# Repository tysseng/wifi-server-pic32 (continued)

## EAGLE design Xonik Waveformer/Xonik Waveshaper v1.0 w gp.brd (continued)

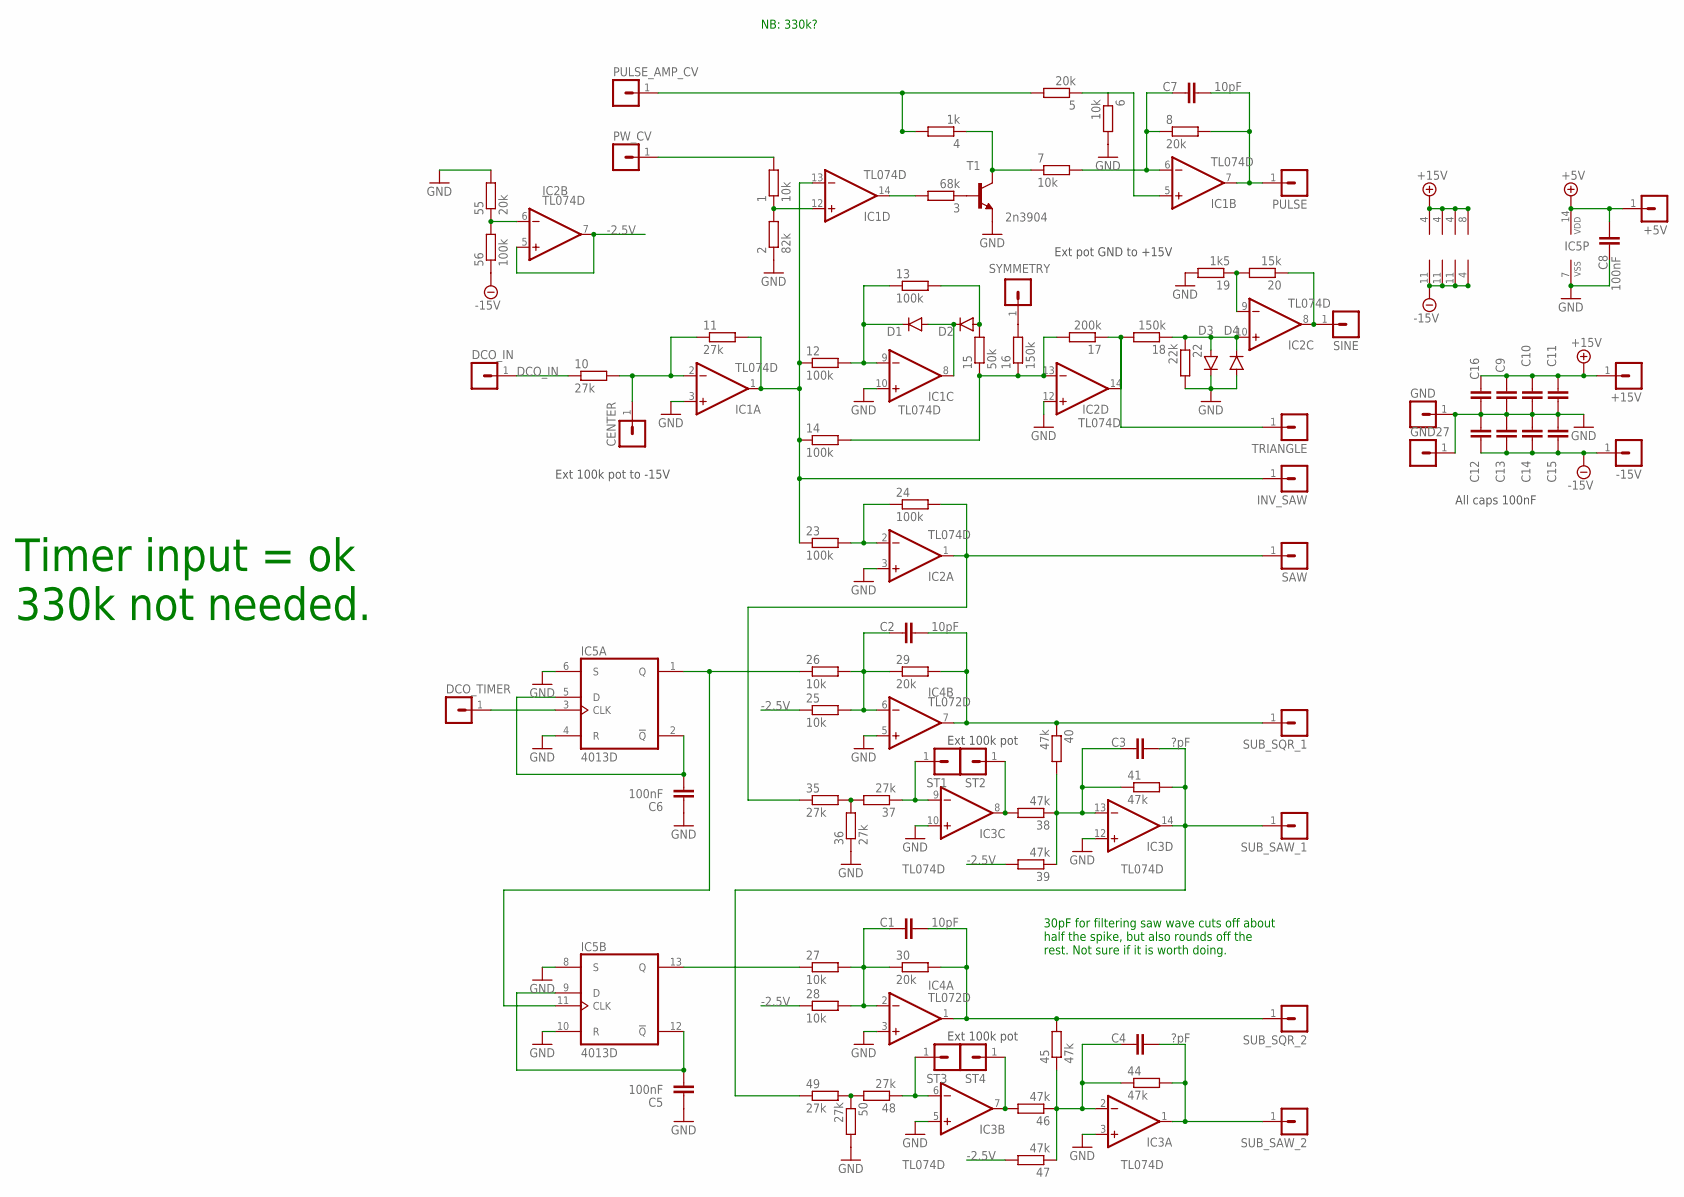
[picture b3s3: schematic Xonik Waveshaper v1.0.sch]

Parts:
1, 6, 7, 25, 26, 27, 28: 10k; R0805
2: 82k; R0805
3: 68k; R0805
4: 1k; R0805
5, 8, 29, 30, 55: 20k; R0805
10, 11, 35, 36, 37, 48, 49, 50: 27k; R0805
12, 13, 14, 23, 24, 56: 100k; R0805
15: 50k; R0805
16, 18: 150k; R0805
17: 200k; R0805
19: 1k5; R0805
20: 15k; R0805
22: 22k; R0805
38, 39, 40, 41, 44, 45, 46, 47: 47k; R0805
+5V, +15V: MA01-1JP; SIP-PIN01-1J
-15V: MA01-1JP; SIP-PIN01-1J
C1, C2, C7: 10pF; C0805
C3, C4: ?pF; C0805
C5, C6, C8: 100nF; C0805
C9, C10, C11, C12, C13, C14, C15, C16: 100nF; C0603K
CENTER: MA01-1JP; SIP-PIN01-1J
D1, D2, D3, D4: 1N41480805; D0805-J
DCO_IN: MA01-1JP; SIP-PIN01-1J
DCO_TIMER: MA01-1JP; SIP-PIN01-1J
GND, GND27: MA01-1JP; SIP-PIN01-1J
IC1, IC2, IC3: TL074D; SO14
IC4: TL072D; SO08J
IC5: 4013D; SO14J
INV_SAW: MA01-1JP; SIP-PIN01-1J
PULSE: MA01-1JP; SIP-PIN01-1J
PULSE_AMP_CV: MA01-1JP; SIP-PIN01-1J
PW_CV: MA01-1JP; SIP-PIN01-1J
SAW: MA01-1JP; SIP-PIN01-1J
SINE: MA01-1JP; SIP-PIN01-1J
ST1, ST2, ST3, ST4: MA01-1JP; SIP-PIN01-1J
SUB_SAW_1, SUB_SAW_2: MA01-1JP; SIP-PIN01-1J
SUB_SQR_1, SUB_SQR_2: MA01-1JP; SIP-PIN01-1J
SYMMETRY: MA01-1JP; SIP-PIN01-1J
T1: 2n3904; SOT23-BEC
TRIANGLE: MA01-1JP; SIP-PIN01-1J

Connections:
+5V: +5V.1, C8.2, IC5.14 (VDD)
+15V: +15V.1, C9.2, C10.2, C11.2, C16.2, IC1.4 (V+), IC2.4 (V+), IC3.4 (V+), IC4.8 (V+)
-2.5V: 25.1, 28.1, 39.2, 47.2, IC2.5 (+IN), IC2.7 (OUT)
-15V: 56.1, -15V.1, C12.1, C13.1, C14.1, C15.1, IC1.11 (V-), IC2.11 (V-), IC3.11 (V-), IC4.4 (V-)
AMP_CV: 4.2, 5.2, PULSE_AMP_CV.1
DCO_IN: 10.1, DCO_IN.1
GND: 2.1, 6.2, 19.2, 22.2, 36.1, 50.2, 55.2, C5.1, C6.1, C8.1, C9.1, C10.1, C11.1, C12.2, C13.2, C14.2, C15.2, C16.1, D3.C, D4.A, GND.1, GND27.1, IC1.3 (+IN), IC1.10 (+IN), IC2.3 (+IN), IC2.12 (+IN), IC3.3 (+IN), IC3.5 (+IN), IC3.10 (+IN), IC3.12 (+IN), IC4.3 (+IN), IC4.5 (+IN), IC5.4 (R), IC5.6 (S), IC5.7 (VSS), IC5.8 (S), IC5.10 (R), T1.E; also elsewhere on the board
unnamed: 1.1, 2.2, IC1.12 (+IN)
unnamed: 3.2, IC1.14 (OUT)
unnamed 9: 3.1, T1.B; also elsewhere on the board
unnamed: 4.1, 7.1, T1.C
unnamed: 5.1, 6.1, IC1.5 (+IN)
unnamed: 7.2, 8.1, C7.1, IC1.6 (-IN)
unnamed: 8.2, C7.2, IC1.7 (OUT), PULSE.1
unnamed: 11.2, 12.1, 14.1, 23.1, IC1.1 (OUT), IC1.13 (-IN), INV_SAW.1
unnamed: 10.2, 11.1, CENTER.1, IC1.2 (-IN)
unnamed: 12.2, 13.1, D1.C, IC1.9 (-IN)
unnamed: D1.A, D2.C, IC1.8 (OUT)
unnamed: 13.2, 15.2, D2.A
unnamed: 14.2, 15.1, 16.1, 17.2, IC2.13 (-IN)
unnamed: 23.2, 24.1, IC2.2 (-IN)
unnamed: 24.2, 35.1, IC2.1 (OUT), SAW.1
unnamed: 25.2, 26.2, 29.1, C2.1, IC4.6 (-IN)
unnamed: 46.2, IC3.7 (OUT), ST4.1
unnamed: 48.2, 49.2, 50.1
unnamed: 27.2, 28.2, 30.1, C1.1, IC4.2 (-IN)
unnamed: 35.2, 36.2, 37.2
unnamed: 37.1, IC3.9 (-IN), ST1.1
unnamed: 38.1, 39.1, 40.2, 41.1, C3.1, IC3.13 (-IN)
unnamed: 41.2, 49.1, C3.2, IC3.14 (OUT), SUB_SAW_1.1
unnamed: 48.1, IC3.6 (-IN), ST3.1
unnamed: 44.1, 45.1, 46.1, 47.1, C4.1, IC3.2 (-IN)
unnamed: 44.2, C4.2, IC3.1 (OUT), SUB_SAW_2.1
unnamed: C6.2, IC5.2 (!Q), IC5.5 (D)
unnamed: 55.1, 56.2, IC2.6 (-IN)
unnamed: C5.2, IC5.9 (D), IC5.12 (!Q)
unnamed: 19.1, 20.2, IC2.9 (-IN)
unnamed: 16.2, SYMMETRY.1
unnamed: 17.1, 18.2, IC2.14 (OUT), TRIANGLE.1
unnamed: 18.1, 22.1, D3.A, D4.C, IC2.10 (+IN)
unnamed: 20.1, IC2.8 (OUT), SINE.1
unnamed: 38.2, IC3.8 (OUT), ST2.1
PW_CV: 1.2, PW_CV.1
SQR: DCO_TIMER.1, IC5.3 (CLK)

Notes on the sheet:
NB: 330k?
All caps 100nF
Ext 100k pot to -15V
Ext pot GND to +15V
Ext 100k pot
Timer input = ok 330k not needed.
30pF for filtering saw wave cuts off about half the spike, but also rounds off the rest. Not sure if it is worth doing.

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
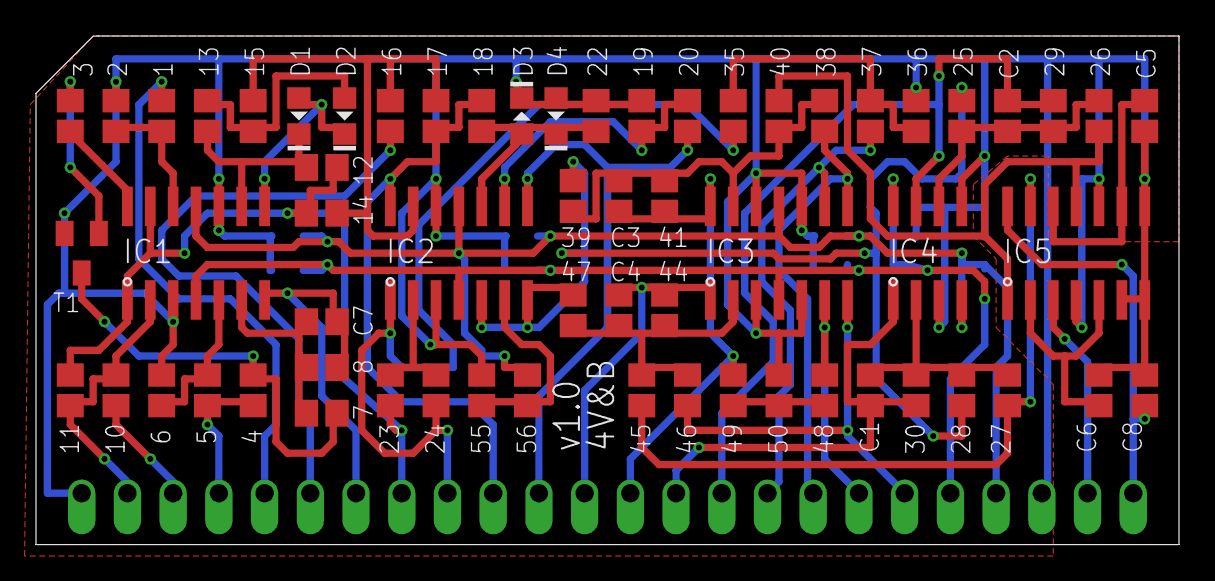
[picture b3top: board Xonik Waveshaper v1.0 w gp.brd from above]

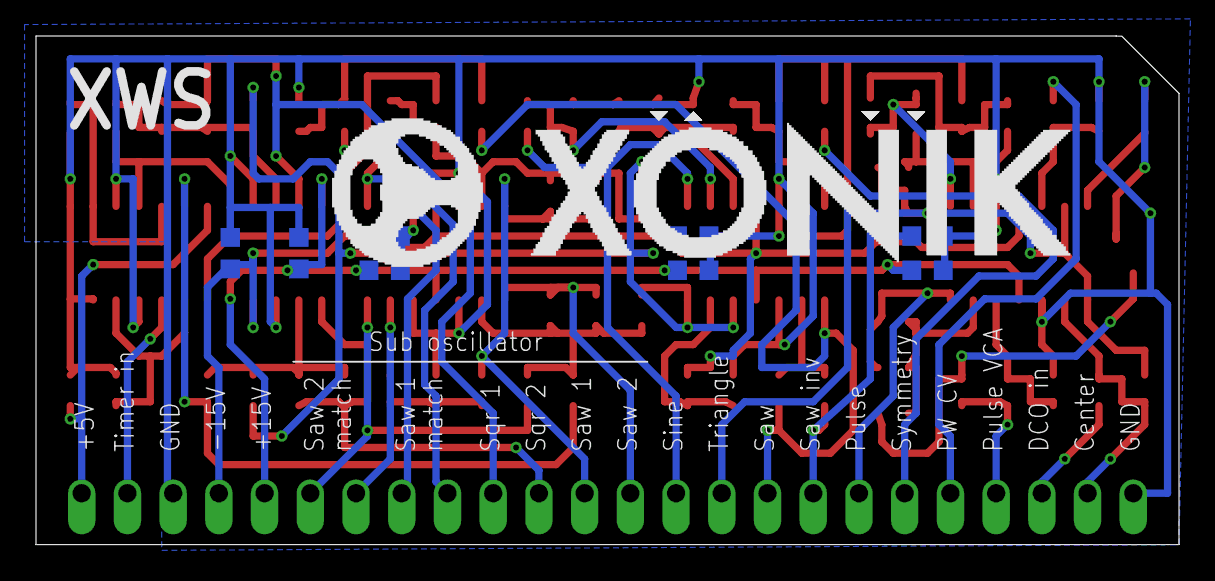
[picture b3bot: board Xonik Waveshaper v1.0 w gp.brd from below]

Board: 2 copper layers, 63.5 x 28.3 mm, 94 parts (8 on the bottom side), 48 nets.
